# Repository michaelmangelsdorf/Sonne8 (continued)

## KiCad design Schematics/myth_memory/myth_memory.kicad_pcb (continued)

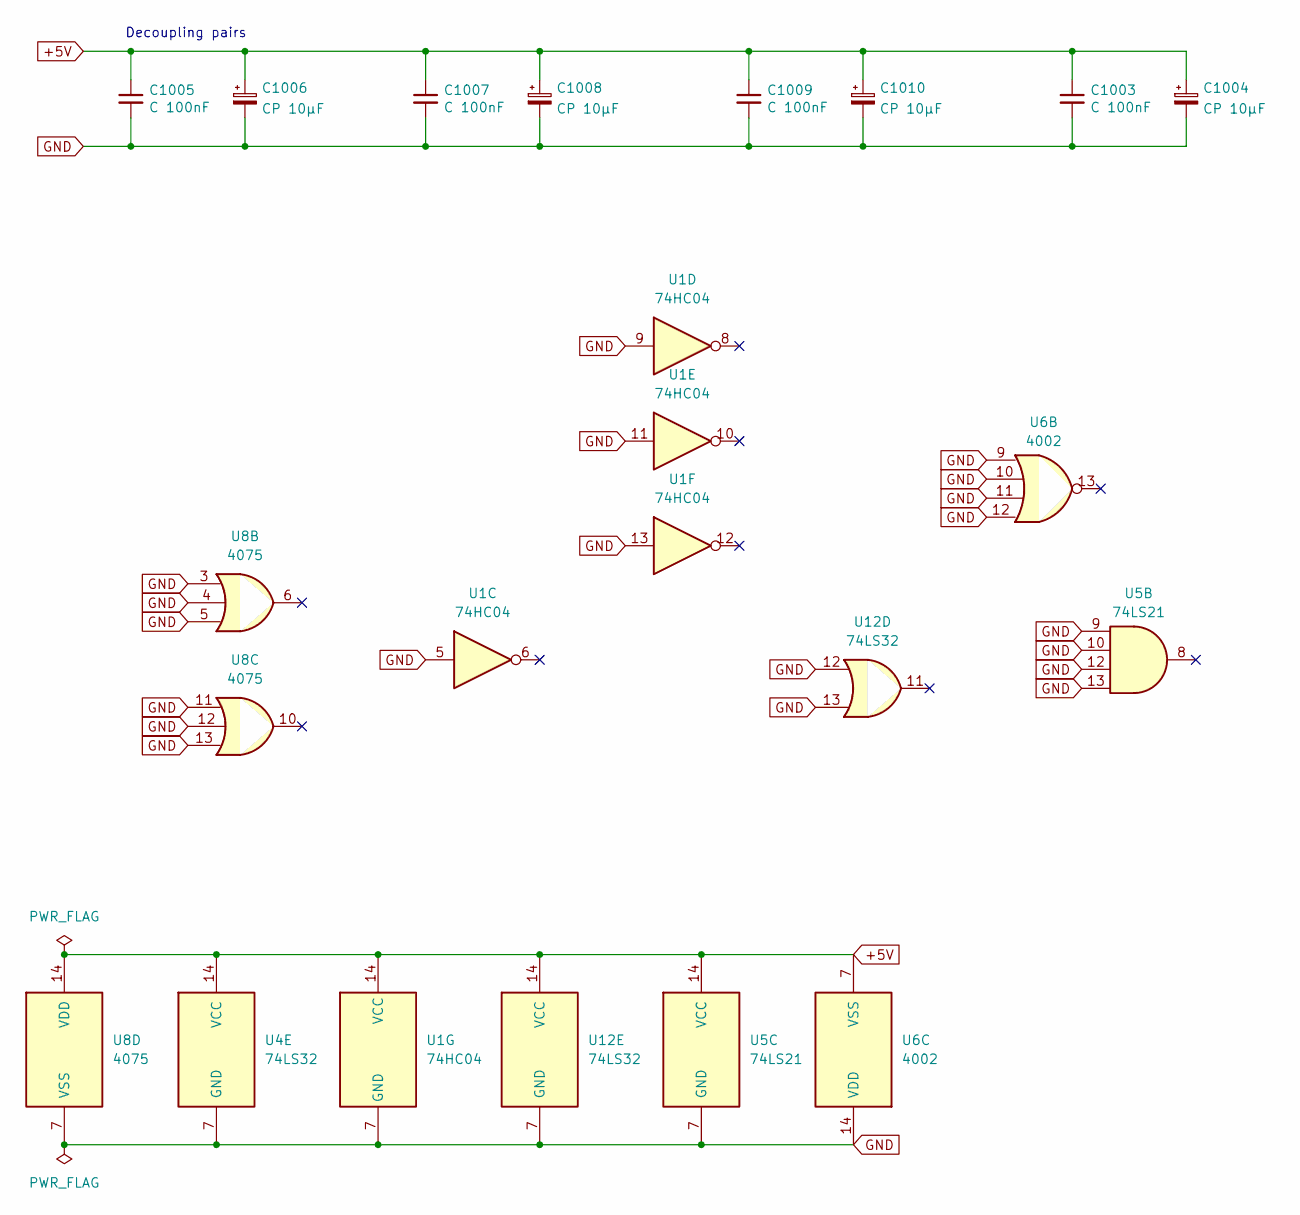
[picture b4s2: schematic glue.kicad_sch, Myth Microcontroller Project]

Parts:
C1003, C1005, C1007, C1009: C 100nF; C_Disc_D5.0mm_W2.5mm_P2.50mm
C1004, C1006, C1008, C1010: CP 10μF; CP_Radial_D6.3mm_P2.50mm
U1: 74HC04; DIP-14_W7.62mm_LongPads
U4, U12: 74LS32; DIP-14_W7.62mm_LongPads
U5: 74LS21; DIP-14_W7.62mm_LongPads
U6: 4002; DIP-14_W7.62mm_LongPads
U8: 4075; DIP-14_W7.62mm_LongPads

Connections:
+5V: C1003.1, C1004.1, C1005.1, C1006.1, C1007.1, C1008.1, C1009.1, C1010.1, U1.14 (VCC), U4.14 (VCC), U5.14 (VCC), U6.7 (VSS), U8.14 (VDD), U12.14 (VCC); also elsewhere on the board
GND: C1003.2, C1004.2, C1005.2, C1006.2, C1007.2, C1008.2, C1009.2, C1010.2, U1.5, U1.7 (GND), U1.9, U1.11, U1.13, U4.7 (GND), U5.7 (GND), U5.9, U5.10, U5.12, U5.13, U6.9, U6.10, U6.11, U6.12, U6.14 (VDD), U8.3, U8.4, U8.5, U8.7 (VSS), U8.11, U8.12, U8.13, U12.7 (GND), U12.12, U12.13; also elsewhere on the board

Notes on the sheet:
Decoupling pairs

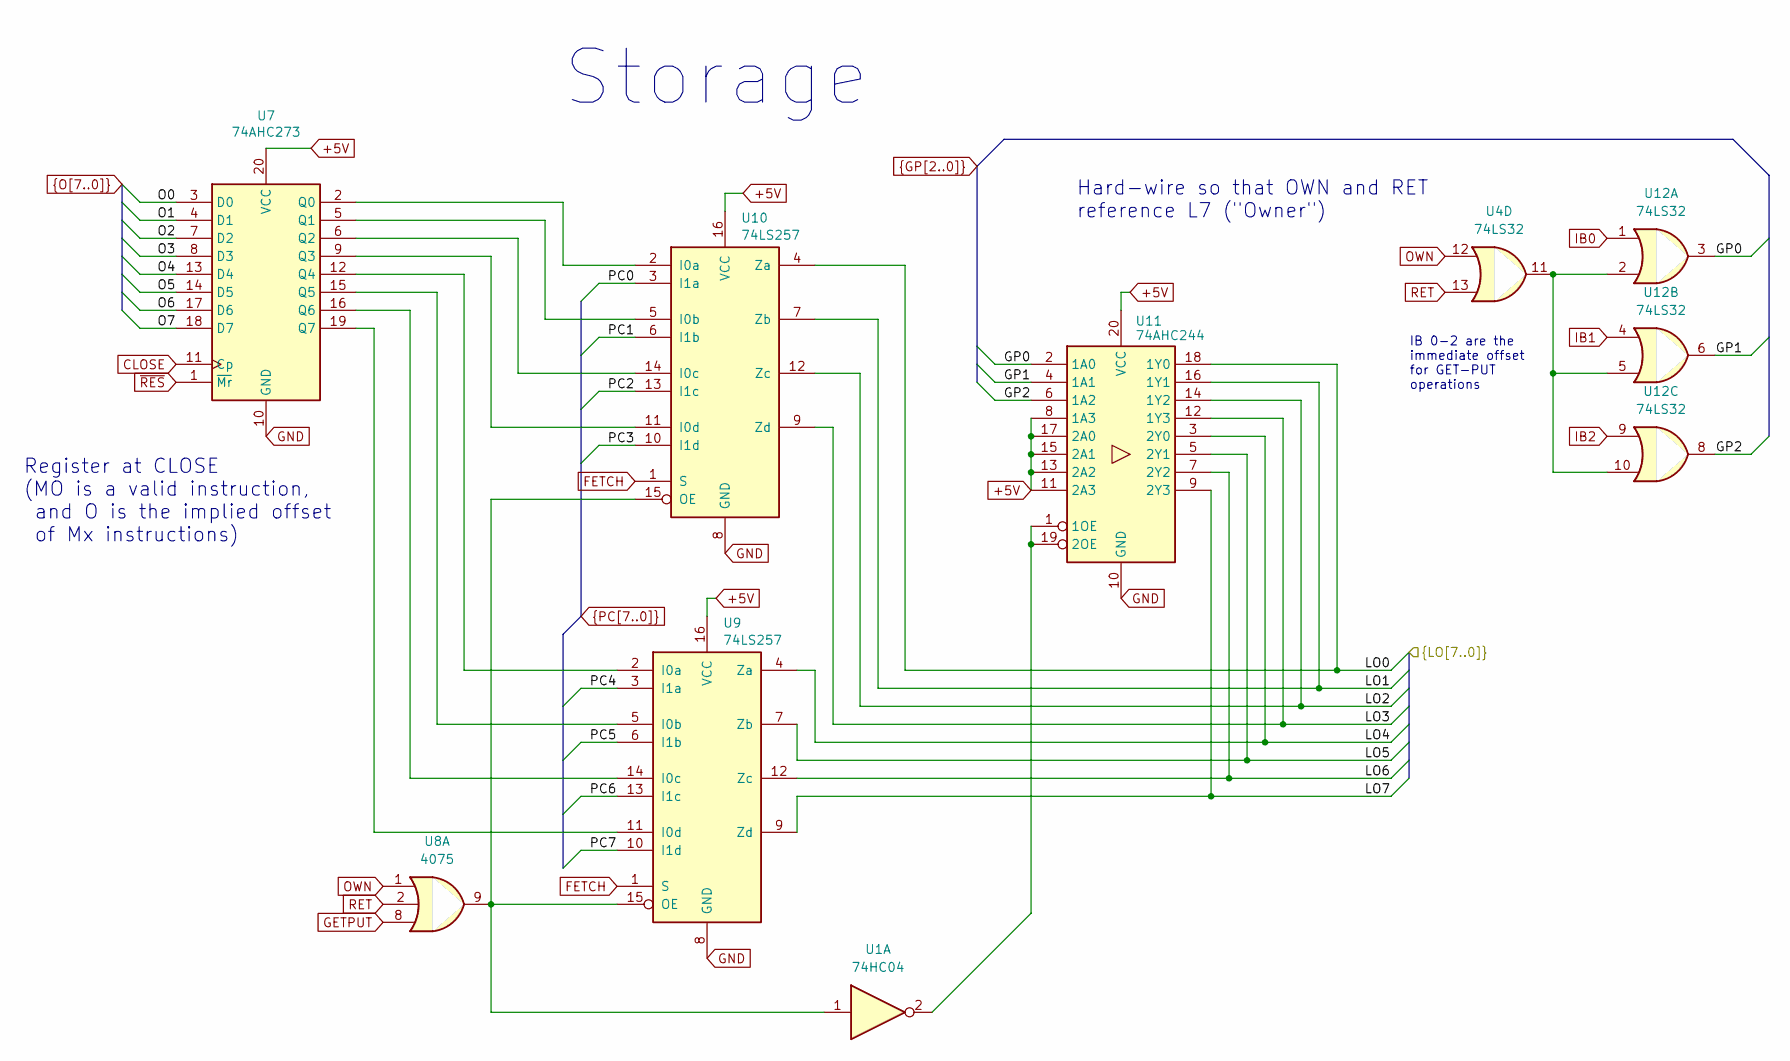
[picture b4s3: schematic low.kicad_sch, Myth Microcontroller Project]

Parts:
U1: 74HC04; DIP-14_W7.62mm_LongPads
U4, U12: 74LS32; DIP-14_W7.62mm_LongPads
U7: 74AHC273; DIP-20_W7.62mm_Socket_LongPads
U8: 4075; DIP-14_W7.62mm_LongPads
U9, U10: 74LS257; DIP-16_W7.62mm_Socket_LongPads
U11: 74AHC244; DIP-20_W7.62mm_Socket_LongPads

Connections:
+5V: U7.20 (VCC), U9.16 (VCC), U10.16 (VCC), U11.8 (1A3), U11.11 (2A3), U11.13 (2A2), U11.15 (2A1), U11.17 (2A0), U11.20 (VCC); also elsewhere on the board
/LO0: U10.4 (Za), U11.18 (1Y0); also elsewhere on the board
/LO1: U10.7 (Zb), U11.16 (1Y1); also elsewhere on the board
/LO2: U10.12 (Zc), U11.14 (1Y2); also elsewhere on the board
/LO3: U10.9 (Zd), U11.12 (1Y3); also elsewhere on the board
/LO4: U9.4 (Za), U11.3 (2Y0); also elsewhere on the board
/LO5: U9.7 (Zb), U11.5 (2Y1); also elsewhere on the board
/LO6: U9.12 (Zc), U11.7 (2Y2); also elsewhere on the board
/LO7: U9.9 (Zd), U11.9 (2Y3); also elsewhere on the board
CLOSE: U7.11 (Cp)
FETCH: U9.1 (S), U10.1 (S); also elsewhere on the board
GETPUT: U8.8; also elsewhere on the board
GND: U7.10 (GND), U9.8 (GND), U10.8 (GND), U11.10 (GND); also elsewhere on the board
GP0: U11.2 (1A0), U12.3
GP1: U11.4 (1A1), U12.6
GP2: U11.6 (1A2), U12.8
IB0: U12.1; also elsewhere on the board
IB1: U12.4; also elsewhere on the board
IB2: U12.9; also elsewhere on the board
unnamed: U7.12 (Q4), U9.2 (I0a)
unnamed: U7.15 (Q5), U9.5 (I0b)
unnamed: U7.16 (Q6), U9.14 (I0c)
unnamed: U7.19 (Q7), U9.11 (I0d)
unnamed: U7.2 (Q0), U10.2 (I0a)
unnamed: U7.5 (Q1), U10.5 (I0b)
unnamed: U7.6 (Q2), U10.14 (I0c)
unnamed: U7.9 (Q3), U10.11 (I0d)
unnamed: U1.1, U8.9, U9.15 (OE), U10.15 (OE)
unnamed: U1.2, U11.1 (1OE), U11.19 (2OE)
unnamed: U4.11, U12.2, U12.5, U12.10
O0: U7.3 (D0); also elsewhere on the board
O1: U7.4 (D1); also elsewhere on the board
O2: U7.7 (D2); also elsewhere on the board
O3: U7.8 (D3); also elsewhere on the board
O4: U7.13 (D4); also elsewhere on the board
O5: U7.14 (D5); also elsewhere on the board
O6: U7.17 (D6); also elsewhere on the board
O7: U7.18 (D7); also elsewhere on the board
OWN: U4.12, U8.1
PC0: U10.3 (I1a); also elsewhere on the board
PC1: U10.6 (I1b); also elsewhere on the board
PC2: U10.13 (I1c); also elsewhere on the board
PC3: U10.10 (I1d); also elsewhere on the board
PC4: U9.3 (I1a); also elsewhere on the board
PC5: U9.6 (I1b); also elsewhere on the board
PC6: U9.13 (I1c); also elsewhere on the board
PC7: U9.10 (I1d); also elsewhere on the board
RET: U4.13, U8.2; also elsewhere on the board
~RES: U7.1 (~Mr); also elsewhere on the board

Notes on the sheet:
Register at CLOSE (MO is a valid instruction, and O is the implied offset of Mx instructions)
Hard-wire so that OWN and RET reference L7 ("Owner")
IB 0-2 are the immediate offset for GET-PUT operations
Storage

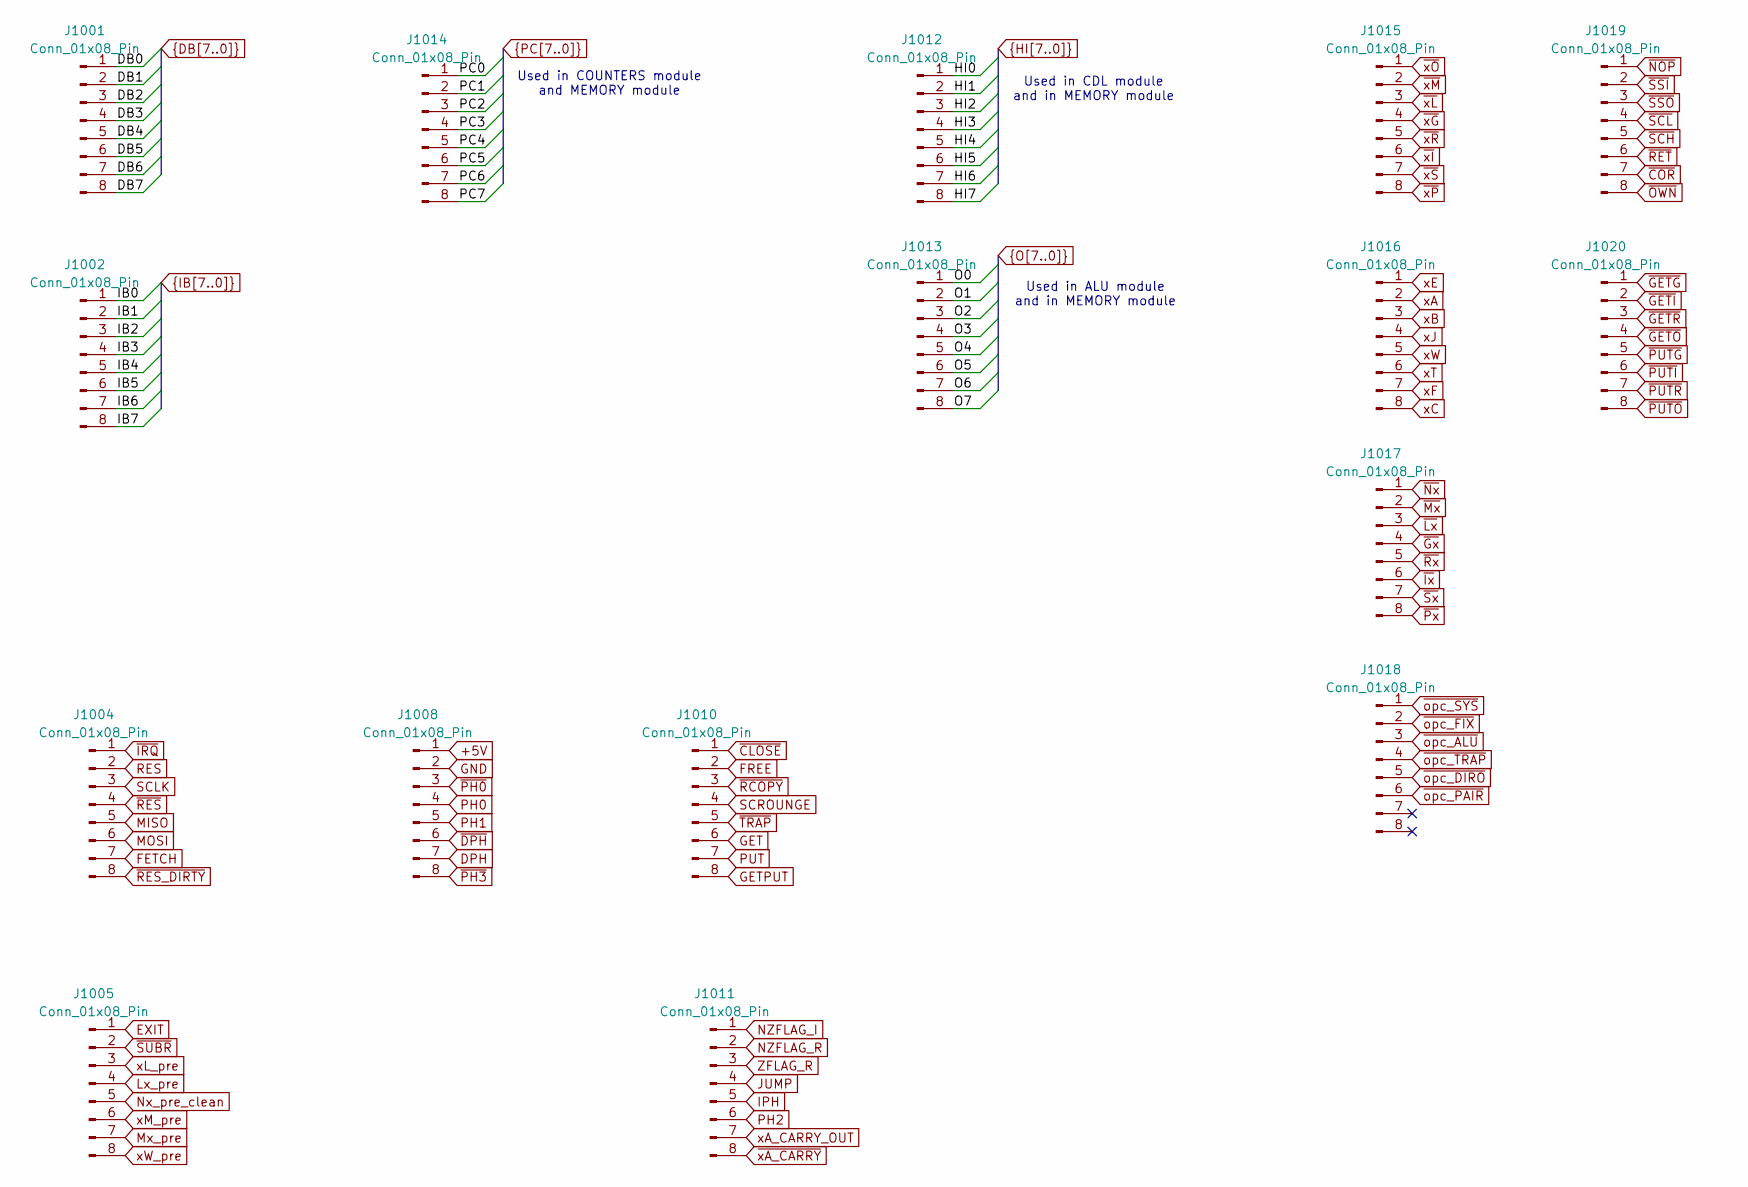
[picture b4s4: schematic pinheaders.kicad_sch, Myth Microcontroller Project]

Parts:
J1001, J1002, J1004, J1005, J1008, J1010, J1011, J1012, J1013, J1014, J1015, J1016, J1017, J1018, J1019, J1020: Conn_01x08_Pin; PinHeader_1x08_P2.54mm_Vertical

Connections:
+5V: J1008.1; also elsewhere on the board
DB0: J1001.1; also elsewhere on the board
DB1: J1001.2; also elsewhere on the board
DB2: J1001.3; also elsewhere on the board
DB3: J1001.4; also elsewhere on the board
DB4: J1001.5; also elsewhere on the board
DB5: J1001.6; also elsewhere on the board
DB6: J1001.7; also elsewhere on the board
DB7: J1001.8; also elsewhere on the board
DPH: J1008.7
EXIT: J1005.1
FETCH: J1004.7; also elsewhere on the board
FREE: J1010.2
GET: J1010.6; also elsewhere on the board
GETPUT: J1010.8; also elsewhere on the board
GND: J1008.2; also elsewhere on the board
HI0: J1012.1; also elsewhere on the board
HI1: J1012.2; also elsewhere on the board
HI2: J1012.3; also elsewhere on the board
HI3: J1012.4; also elsewhere on the board
HI4: J1012.5; also elsewhere on the board
HI5: J1012.6; also elsewhere on the board
HI6: J1012.7; also elsewhere on the board
HI7: J1012.8; also elsewhere on the board
IB0: J1002.1; also elsewhere on the board
IB1: J1002.2; also elsewhere on the board
IB2: J1002.3; also elsewhere on the board
IB3: J1002.4
IB4: J1002.5
IB5: J1002.6
IB6: J1002.7
IB7: J1002.8
IPH: J1011.5; also elsewhere on the board
JUMP: J1011.4
Lx_pre: J1005.4
MISO: J1004.5
MOSI: J1004.6
Mx_pre: J1005.7
NZFLAG_I: J1011.1
NZFLAG_R: J1011.2
Nx_pre_clean: J1005.5
O0: J1013.1; also elsewhere on the board
O1: J1013.2; also elsewhere on the board
O2: J1013.3; also elsewhere on the board
O3: J1013.4; also elsewhere on the board
O4: J1013.5; also elsewhere on the board
O5: J1013.6; also elsewhere on the board
O6: J1013.7; also elsewhere on the board
O7: J1013.8; also elsewhere on the board
PC0: J1014.1; also elsewhere on the board
PC1: J1014.2; also elsewhere on the board
PC2: J1014.3; also elsewhere on the board
PC3: J1014.4; also elsewhere on the board
PC4: J1014.5; also elsewhere on the board
PC5: J1014.6; also elsewhere on the board
PC6: J1014.7; also elsewhere on the board
PC7: J1014.8; also elsewhere on the board
PH0: J1008.4
PH1: J1008.5
PH2: J1011.6
PUT: J1010.7
RES: J1004.2
SCLK: J1004.3
SCROUNGE: J1010.4
ZFLAG_R: J1011.3
xA: J1016.2
xA_CARRY_OUT: J1011.7
xB: J1016.3
xC: J1016.8
xE: J1016.1
xF: J1016.7
xJ: J1016.4
xL_pre: J1005.3
xM_pre: J1005.6
xT: J1016.6
xW: J1016.5
xW_pre: J1005.8
~CLOSE: J1010.1
~COR: J1019.7
~DPH: J1008.6
~Dx: J1017.4
~GETD: J1020.1
~GETI: J1020.2
~GETO: J1020.4
~GETR: J1020.3
~IRQ: J1004.1
~Ix: J1017.6
~Lx: J1017.3
~Mx: J1017.2
~NOP: J1019.1
~Nx: J1017.1
~OWN: J1019.8; also elsewhere on the board
~PH0: J1008.3
~PH3: J1008.8; also elsewhere on the board
~PUTD: J1020.5
~PUTI: J1020.6
~PUTO: J1020.8
~PUTR: J1020.7
~Px: J1017.8
~RCOPY: J1010.3
~RES_DIRTY: J1004.8
~RES: J1004.4; also elsewhere on the board
~RET: J1019.6
~Rx: J1017.5
~SCH: J1019.5
~SCL: J1019.4
~SSI: J1019.2
~SSO: J1019.3
~SUBR: J1005.2
~Sx: J1017.7
~TRAP: J1010.5
~opc_ALU: J1018.3
~opc_DIRO: J1018.5
~opc_FIX: J1018.2
~opc_PAIR: J1018.6
~opc_SYS: J1018.1
~opc_TRAP: J1018.4
~xA_CARRY: J1011.8
~xD: J1015.4
~xI: J1015.6
~xL: J1015.3; also elsewhere on the board
~xM: J1015.2; also elsewhere on the board
~xO: J1015.1
~xP: J1015.8
~xR: J1015.5
~xS: J1015.7

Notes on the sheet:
Used in COUNTERS module and MEMORY module
Used in CDL module and in MEMORY module
Used in ALU module and in MEMORY module

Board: 2 copper layers, 38 parts (0 on the bottom side), 75 nets, no tracks yet.

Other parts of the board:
U2: KM62256CLP; DIP-28_W15.24mm_LongPads

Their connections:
+5V: U2.28 (VCC); also elsewhere on the board
/LO0: U2.10 (A0); also elsewhere on the board
/LO1: U2.9 (A1); also elsewhere on the board
/LO2: U2.8 (A2); also elsewhere on the board
/LO3: U2.7 (A3); also elsewhere on the board
/LO4: U2.6 (A4); also elsewhere on the board
/LO5: U2.5 (A5); also elsewhere on the board
/LO6: U2.4 (A6); also elsewhere on the board
/LO7: U2.3 (A7); also elsewhere on the board
/~IN_RAM: U2.20 (~CS); also elsewhere on the board
DB0: U2.11 (Q0); also elsewhere on the board
DB1: U2.12 (Q1); also elsewhere on the board
DB2: U2.13 (Q2); also elsewhere on the board
DB3: U2.15 (Q3); also elsewhere on the board
DB4: U2.16 (Q4); also elsewhere on the board
DB5: U2.17 (Q5); also elsewhere on the board
DB6: U2.18 (Q6); also elsewhere on the board
DB7: U2.19 (Q7); also elsewhere on the board
GND: U2.14 (GND); also elsewhere on the board
HI0: U2.25 (A8); also elsewhere on the board
HI1: U2.24 (A9); also elsewhere on the board
HI2: U2.21 (A10); also elsewhere on the board
HI3: U2.23 (A11); also elsewhere on the board
HI4: U2.2 (A12); also elsewhere on the board
HI5: U2.26 (A13); also elsewhere on the board
HI6: U2.1 (A14); also elsewhere on the board
unnamed 55: U2.22 (~OE); also elsewhere on the board
unnamed 56: U2.27 (~WE); also elsewhere on the board

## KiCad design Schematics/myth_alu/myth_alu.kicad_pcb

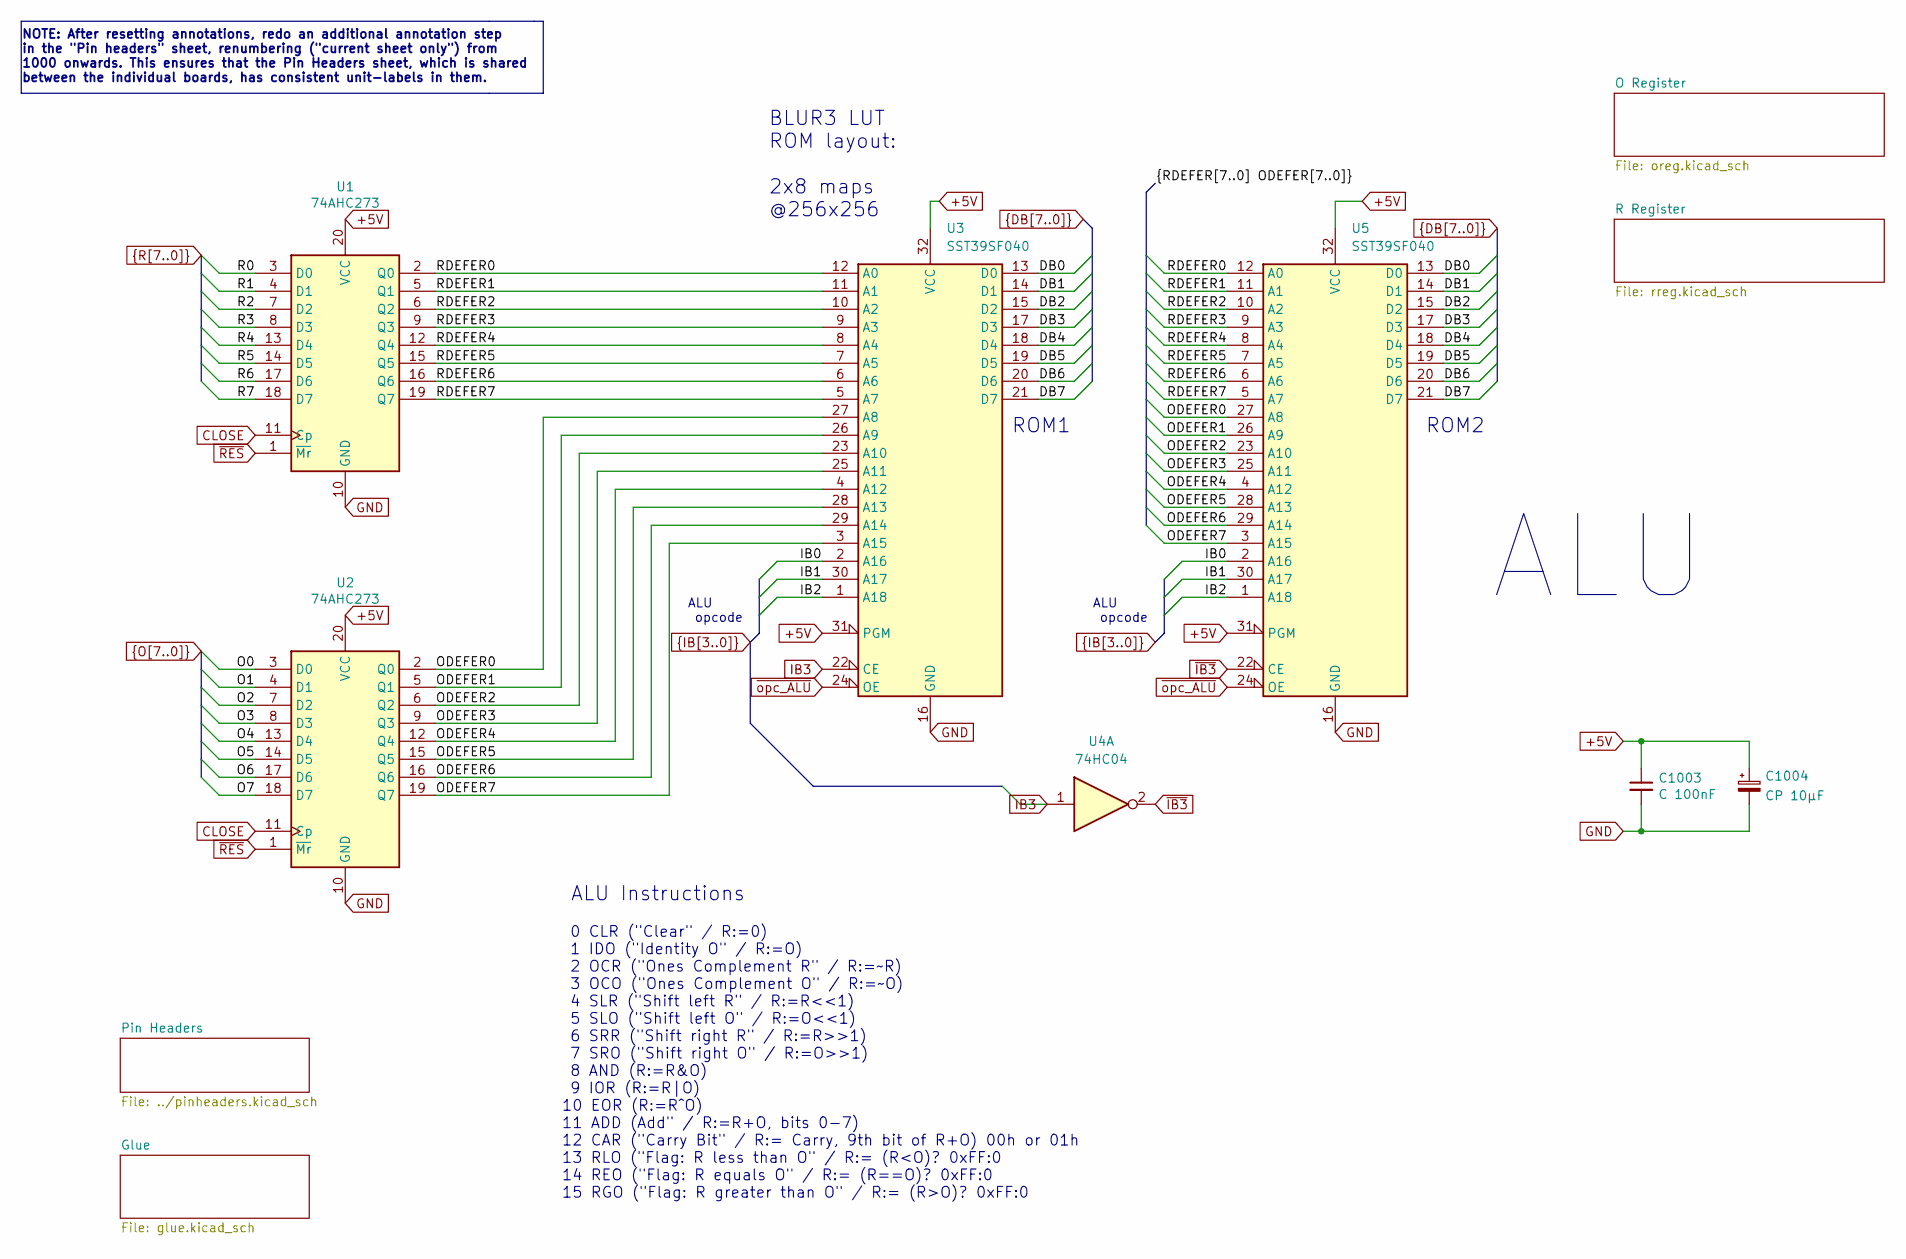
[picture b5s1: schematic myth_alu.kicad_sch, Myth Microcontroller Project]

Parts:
C1003: C 100nF; C_Disc_D5.0mm_W2.5mm_P2.50mm
C1004: CP 10μF; CP_Radial_D6.3mm_P2.50mm
U1, U2: 74AHC273; DIP-20_W7.62mm_Socket_LongPads
U3, U5: SST39SF040; DIP-32_W15.24mm_Socket_LongPads
U4: 74HC04; DIP-14_W7.62mm_Socket_LongPads

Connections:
+5V: C1003.1, C1004.1, U1.20 (VCC), U2.20 (VCC), U3.31 (PGM), U3.32 (VCC), U5.31 (PGM), U5.32 (VCC); also elsewhere on the board
/ODEFER0: U2.2 (Q0), U3.27 (A8), U5.27 (A8)
/ODEFER1: U2.5 (Q1), U3.26 (A9), U5.26 (A9)
/ODEFER2: U2.6 (Q2), U3.23 (A10), U5.23 (A10)
/ODEFER3: U2.9 (Q3), U3.25 (A11), U5.25 (A11)
/ODEFER4: U2.12 (Q4), U3.4 (A12), U5.4 (A12)
/ODEFER5: U2.15 (Q5), U3.28 (A13), U5.28 (A13)
/ODEFER6: U2.16 (Q6), U3.29 (A14), U5.29 (A14)
/ODEFER7: U2.19 (Q7), U3.3 (A15), U5.3 (A15)
/RDEFER0: U1.2 (Q0), U3.12 (A0), U5.12 (A0)
/RDEFER1: U1.5 (Q1), U3.11 (A1), U5.11 (A1)
/RDEFER2: U1.6 (Q2), U3.10 (A2), U5.10 (A2)
/RDEFER3: U1.9 (Q3), U3.9 (A3), U5.9 (A3)
/RDEFER4: U1.12 (Q4), U3.8 (A4), U5.8 (A4)
/RDEFER5: U1.15 (Q5), U3.7 (A5), U5.7 (A5)
/RDEFER6: U1.16 (Q6), U3.6 (A6), U5.6 (A6)
/RDEFER7: U1.19 (Q7), U3.5 (A7), U5.5 (A7)
CLOSE: U1.11 (Cp), U2.11 (Cp)
DB0: U3.13 (D0), U5.13 (D0); also elsewhere on the board
DB1: U3.14 (D1), U5.14 (D1); also elsewhere on the board
DB2: U3.15 (D2), U5.15 (D2); also elsewhere on the board
DB3: U3.17 (D3), U5.17 (D3); also elsewhere on the board
DB4: U3.18 (D4), U5.18 (D4); also elsewhere on the board
DB5: U3.19 (D5), U5.19 (D5); also elsewhere on the board
DB6: U3.20 (D6), U5.20 (D6); also elsewhere on the board
DB7: U3.21 (D7), U5.21 (D7); also elsewhere on the board
GND: C1003.2, C1004.2, U1.10 (GND), U2.10 (GND), U3.16 (GND), U5.16 (GND); also elsewhere on the board
IB0: U3.2 (A16), U5.2 (A16); also elsewhere on the board
IB1: U3.30 (A17), U5.30 (A17); also elsewhere on the board
IB2: U3.1 (A18), U5.1 (A18); also elsewhere on the board
IB3: U3.22 (CE), U4.1; also elsewhere on the board
O0: U2.3 (D0); also elsewhere on the board
O1: U2.4 (D1); also elsewhere on the board
O2: U2.7 (D2); also elsewhere on the board
O3: U2.8 (D3); also elsewhere on the board
O4: U2.13 (D4); also elsewhere on the board
O5: U2.14 (D5); also elsewhere on the board
O6: U2.17 (D6); also elsewhere on the board
O7: U2.18 (D7); also elsewhere on the board
R0: U1.3 (D0); also elsewhere on the board
R1: U1.4 (D1); also elsewhere on the board
R2: U1.7 (D2); also elsewhere on the board
R3: U1.8 (D3); also elsewhere on the board
R4: U1.13 (D4); also elsewhere on the board
R5: U1.14 (D5); also elsewhere on the board
R6: U1.17 (D6); also elsewhere on the board
R7: U1.18 (D7); also elsewhere on the board
~IB3: U4.2, U5.22 (CE)
~RES: U1.1 (~Mr), U2.1 (~Mr); also elsewhere on the board
~opc_ALU: U3.24 (OE), U5.24 (OE); also elsewhere on the board

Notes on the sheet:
BLUR3 LUT ROM layout: 2x8 maps @256x256
ALU opcode
NOTE: After resetting annotations, redo an additional annotation step in the "Pin headers" sheet, renumbering ("current sheet only") from 1000 onwards. This ensures that the Pin Headers sheet, which is shared between the individual boards, has consistent unit-labels in them.
0 CLR ("Clear" / R:=0) 1 IDO ("Identity O" / R:=O) 2 OCR ("Ones Complement R" / R:=~R) 3 OCO ("Ones Complement O" / R:=~O) 4 SLR ("Shift left R" / R:=R<<1) 5 SLO ("Shift left O" / R:=O<<1) 6 SRR ("Shift right R" / R:=R>>1) 7 SRO ("Shift right O" / R:=O>>1) 8 AND (R:=R&O) 9 IOR (R:=R|O) 10 EOR (R:=R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
ALU
ROM1
ALU Instructions
ROM2

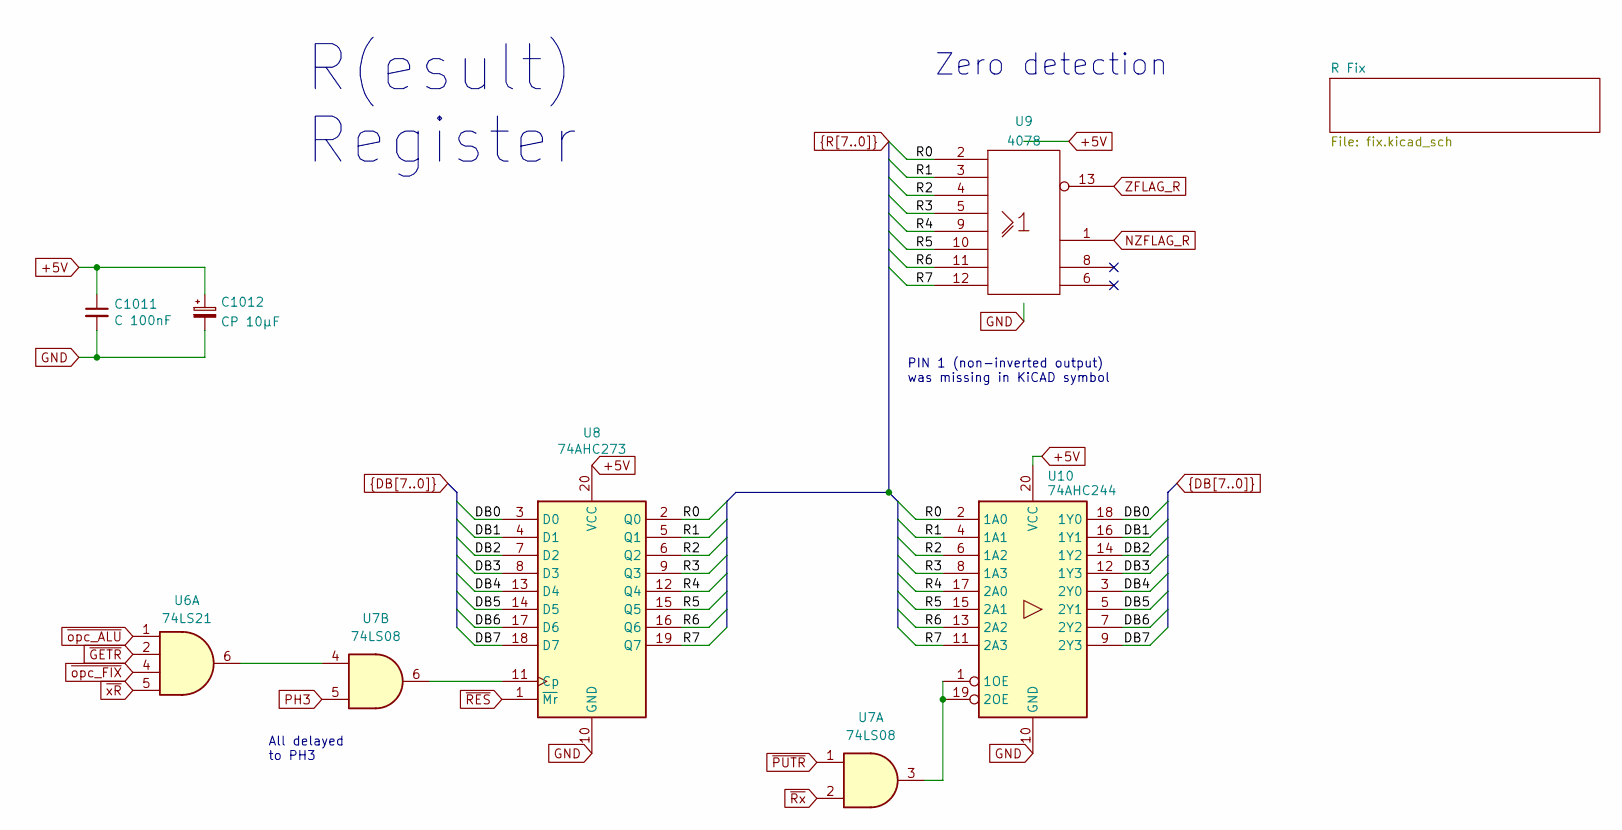
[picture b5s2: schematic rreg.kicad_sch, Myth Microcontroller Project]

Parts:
C1011: C 100nF; C_Disc_D5.0mm_W2.5mm_P2.50mm
C1012: CP 10μF; CP_Radial_D6.3mm_P2.50mm
U6: 74LS21; DIP-14_W7.62mm_Socket_LongPads
U7: 74LS08; DIP-14_W7.62mm_Socket_LongPads
U8: 74AHC273; DIP-20_W7.62mm_Socket_LongPads
U9: 4078; DIP-14_W7.62mm_Socket_LongPads
U10: 74AHC244; DIP-20_W7.62mm_Socket_LongPads

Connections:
+5V: C1011.1, C1012.1, U8.20 (VCC), U9.14 (Vdd), U10.20 (VCC); also elsewhere on the board
DB0: U8.3 (D0), U10.18 (1Y0); also elsewhere on the board
DB1: U8.4 (D1), U10.16 (1Y1); also elsewhere on the board
DB2: U8.7 (D2), U10.14 (1Y2); also elsewhere on the board
DB3: U8.8 (D3), U10.12 (1Y3); also elsewhere on the board
DB4: U8.13 (D4), U10.3 (2Y0); also elsewhere on the board
DB5: U8.14 (D5), U10.5 (2Y1); also elsewhere on the board
DB6: U8.17 (D6), U10.7 (2Y2); also elsewhere on the board
DB7: U8.18 (D7), U10.9 (2Y3); also elsewhere on the board
GND: C1011.2, C1012.2, U8.10 (GND), U9.7 (Vss), U10.10 (GND); also elsewhere on the board
NZFLAG_R: U9.1; also elsewhere on the board
unnamed: U6.6, U7.4
unnamed: U7.6, U8.11 (Cp)
unnamed: U7.3, U10.1 (1OE), U10.19 (2OE)
PH3: U7.5
R0: U8.2 (Q0), U9.2, U10.2 (1A0); also elsewhere on the board
R1: U8.5 (Q1), U9.3, U10.4 (1A1); also elsewhere on the board
R2: U8.6 (Q2), U9.4, U10.6 (1A2); also elsewhere on the board
R3: U8.9 (Q3), U9.5, U10.8 (1A3); also elsewhere on the board
R4: U8.12 (Q4), U9.9, U10.17 (2A0); also elsewhere on the board
R5: U8.15 (Q5), U9.10, U10.15 (2A1); also elsewhere on the board
R6: U8.16 (Q6), U9.11, U10.13 (2A2); also elsewhere on the board
R7: U8.19 (Q7), U9.12, U10.11 (2A3); also elsewhere on the board
ZFLAG_R: U9.13; also elsewhere on the board
~GETR: U6.2; also elsewhere on the board
~PUTR: U7.1; also elsewhere on the board
~RES: U8.1 (~Mr); also elsewhere on the board
~Rx: U7.2; also elsewhere on the board
~opc_ALU: U6.1; also elsewhere on the board
~opc_FIX: U6.4; also elsewhere on the board
~xR: U6.5; also elsewhere on the board

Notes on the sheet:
Zero detection
R(esult) Register
PIN 1 (non-inverted output) was missing in KiCAD symbol
All delayed to PH3

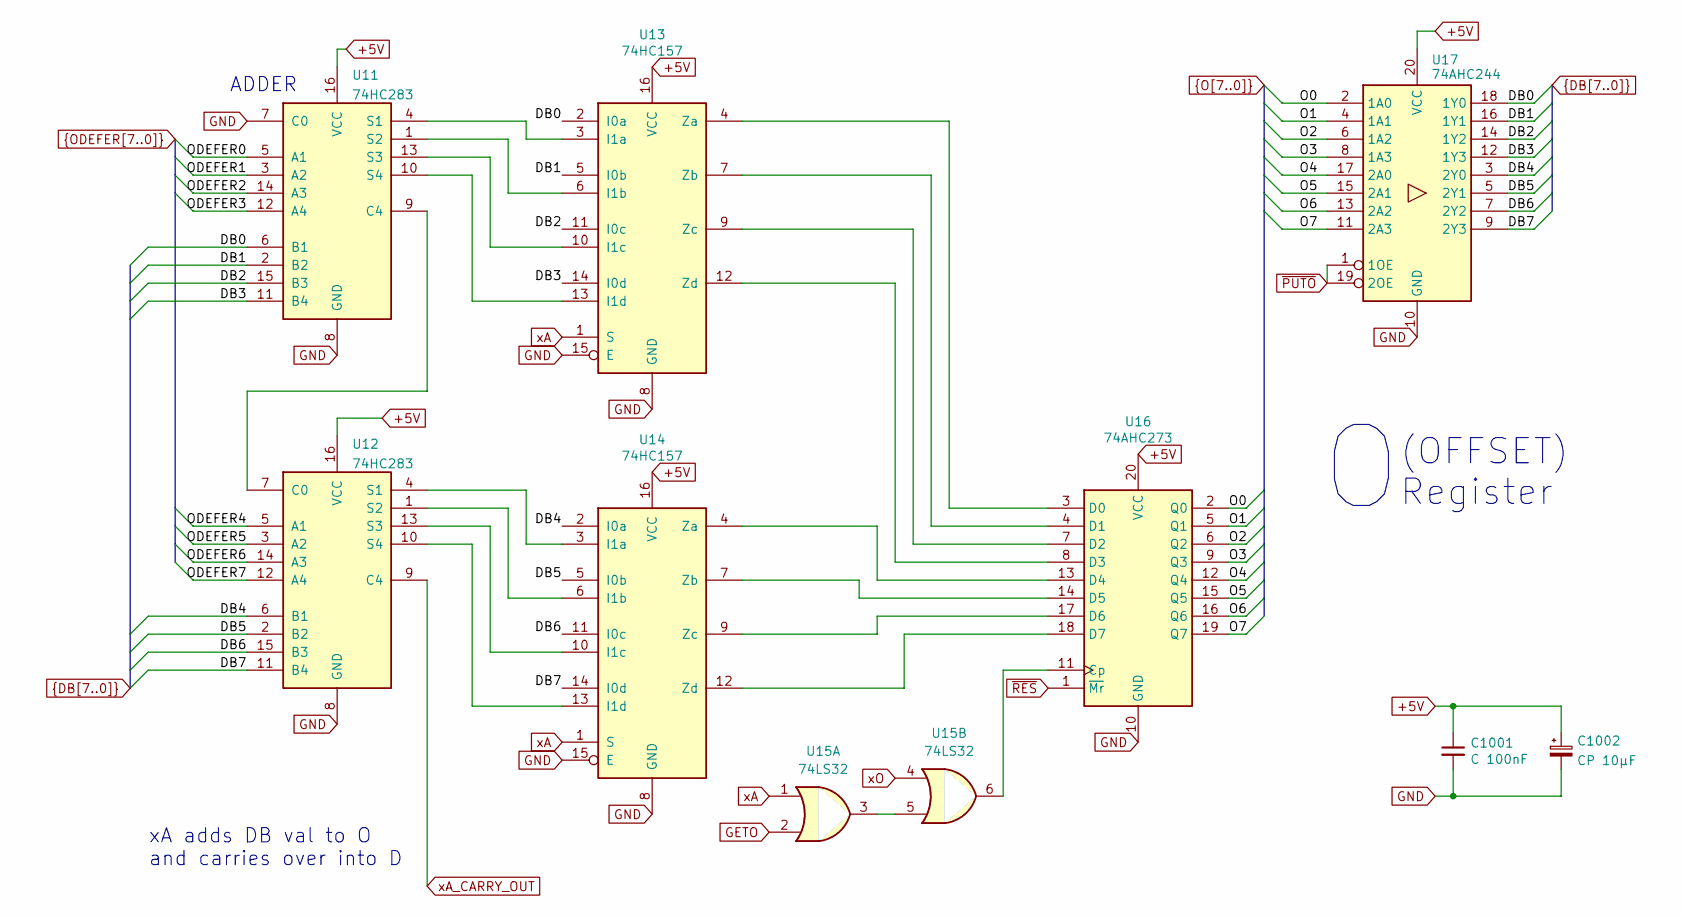
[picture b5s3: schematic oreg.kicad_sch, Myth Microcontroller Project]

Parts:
C1001: C 100nF; C_Disc_D5.0mm_W2.5mm_P2.50mm
C1002: CP 10μF; CP_Radial_D6.3mm_P2.50mm
U11, U12: 74HC283; DIP-16_W7.62mm_Socket_LongPads
U13, U14: 74HC157; DIP-16_W7.62mm_Socket_LongPads
U15: 74LS32; DIP-14_W7.62mm_Socket_LongPads
U16: 74AHC273; DIP-20_W7.62mm_Socket_LongPads
U17: 74AHC244; DIP-20_W7.62mm_Socket_LongPads

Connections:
+5V: C1001.1, C1002.1, U11.16 (VCC), U12.16 (VCC), U13.16 (VCC), U14.16 (VCC), U16.20 (VCC), U17.20 (VCC); also elsewhere on the board
DB0: U11.6 (B1), U13.2 (I0a), U17.18 (1Y0); also elsewhere on the board
DB1: U11.2 (B2), U13.5 (I0b), U17.16 (1Y1); also elsewhere on the board
DB2: U11.15 (B3), U13.11 (I0c), U17.14 (1Y2); also elsewhere on the board
DB3: U11.11 (B4), U13.14 (I0d), U17.12 (1Y3); also elsewhere on the board
DB4: U12.6 (B1), U14.2 (I0a), U17.3 (2Y0); also elsewhere on the board
DB5: U12.2 (B2), U14.5 (I0b), U17.5 (2Y1); also elsewhere on the board
DB6: U12.15 (B3), U14.11 (I0c), U17.7 (2Y2); also elsewhere on the board
DB7: U12.11 (B4), U14.14 (I0d), U17.9 (2Y3); also elsewhere on the board
GETO: U15.2
GND: C1001.2, C1002.2, U11.7 (C0), U11.8 (GND), U12.8 (GND), U13.8 (GND), U13.15 (E), U14.8 (GND), U14.15 (E), U16.10 (GND), U17.10 (GND); also elsewhere on the board
unnamed: U11.9 (C4), U12.7 (C0)
unnamed: U11.4 (S1), U13.3 (I1a)
unnamed: U11.1 (S2), U13.6 (I1b)
unnamed: U11.13 (S3), U13.10 (I1c)
unnamed: U11.10 (S4), U13.13 (I1d)
unnamed: U12.4 (S1), U14.3 (I1a)
unnamed: U12.1 (S2), U14.6 (I1b)
unnamed: U12.13 (S3), U14.10 (I1c)
unnamed: U12.10 (S4), U14.13 (I1d)
unnamed: U13.4 (Za), U16.3 (D0)
unnamed: U13.7 (Zb), U16.4 (D1)
unnamed: U13.9 (Zc), U16.7 (D2)
unnamed: U13.12 (Zd), U16.8 (D3)
unnamed: U14.4 (Za), U16.13 (D4)
unnamed: U14.7 (Zb), U16.14 (D5)
unnamed: U14.9 (Zc), U16.17 (D6)
unnamed: U14.12 (Zd), U16.18 (D7)
unnamed: U15.3, U15.5
unnamed: U15.6, U16.11 (Cp)
O0: U16.2 (Q0), U17.2 (1A0); also elsewhere on the board
O1: U16.5 (Q1), U17.4 (1A1); also elsewhere on the board
O2: U16.6 (Q2), U17.6 (1A2); also elsewhere on the board
O3: U16.9 (Q3), U17.8 (1A3); also elsewhere on the board
O4: U16.12 (Q4), U17.17 (2A0); also elsewhere on the board
O5: U16.15 (Q5), U17.15 (2A1); also elsewhere on the board
O6: U16.16 (Q6), U17.13 (2A2); also elsewhere on the board
O7: U16.19 (Q7), U17.11 (2A3); also elsewhere on the board
ODEFER0: U11.5 (A1)
ODEFER1: U11.3 (A2)
ODEFER2: U11.14 (A3)
ODEFER3: U11.12 (A4)
ODEFER4: U12.5 (A1)
ODEFER5: U12.3 (A2)
ODEFER6: U12.14 (A3)
ODEFER7: U12.12 (A4)
xA: U13.1 (S), U14.1 (S), U15.1; also elsewhere on the board
xA_CARRY_OUT: U12.9 (C4); also elsewhere on the board
xO: U15.4
~PUTO: U17.1 (1OE), U17.19 (2OE); also elsewhere on the board
~RES: U16.1 (~Mr); also elsewhere on the board

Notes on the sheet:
xA adds DB val to O and carries over into D
ADDER
(OFFSET) Register
